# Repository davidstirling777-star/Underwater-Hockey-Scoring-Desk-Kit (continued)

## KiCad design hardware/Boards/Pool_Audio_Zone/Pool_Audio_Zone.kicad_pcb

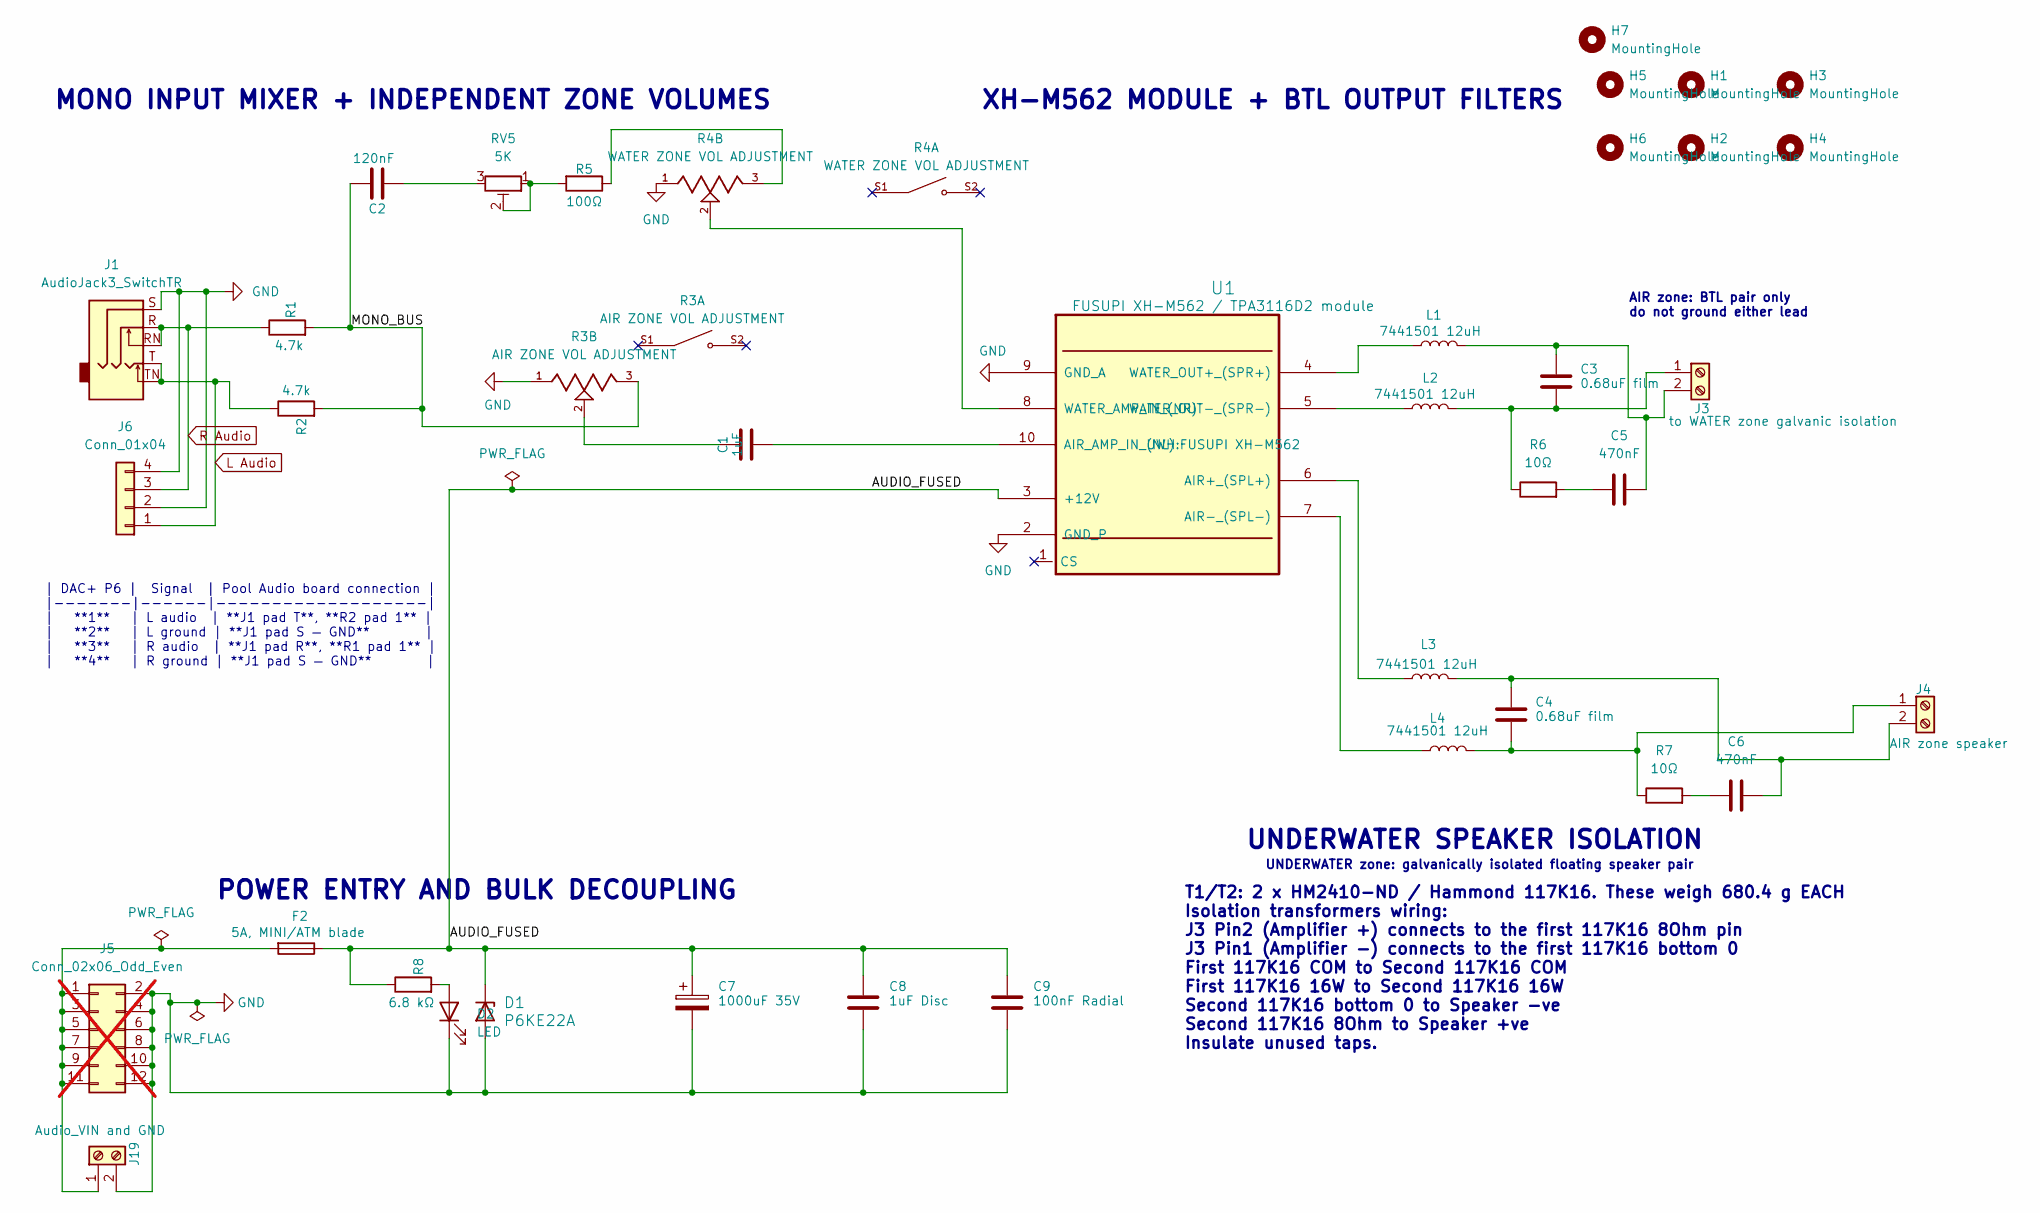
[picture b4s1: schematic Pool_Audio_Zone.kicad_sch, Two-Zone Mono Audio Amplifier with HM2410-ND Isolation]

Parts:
C1: 1uF; C_Rect_L7.2mm_W4.5mm_P5.00mm; MPN B32529C0105J000
C2: 120nF; C_Rect_L7.2mm_W3.5mm_P5.00mm; MPN R82EC3120DQ70J
C3, C4: 0.68uF film; C_Rect_L18.0mm_W9.0mm_P15.00mm_FKS3_FKP3; MPN B32652A3684K000
C5, C6: 470nF; C_Rect_L18.0mm_W9.0mm_P15.00mm_FKS3_FKP3; MPN B32672L4474J000
C7: 1000uF 35V; CP_Radial_D12.5mm_P5.00mm; MPN 35ZLH1000MEFC12.5X20
C8: 1uF Disc; C_Disc_D6.0mm_W4.4mm_P5.00mm; MPN RCER71H105K2K1H03B
C9: 100nF Radial; C_Disc_D4.7mm_W2.5mm_P5.00mm; MPN RDER71H104K0M1H03A
D1: P6KE22A; D_DO-15_P10.16mm_Horizontal; MPN P6KE22A
D2: LED; LED_D3.0mm; MPN WP710A10LCGDK
F2: 5A, MINI/ATM blade; Fuseholder_Blade_Mini_Keystone_3568; MPN 3568
H1, H2, H3, H4, H5, H6, H7: MountingHole; MountingHole_3.2mm_M3
J1: AudioJack3_SwitchTR; Jack_3.5mm_CUI_SJ1-3525N_Horizontal; MPN SJ1-3525N
J3: to WATER zone galvanic isolation; TerminalBlock_CUI_TB007-508-02_1x02_P5.08mm_Horizontal; MPN TB007-508-02BE
J4: AIR zone speaker; TerminalBlock_CUI_TB007-508-02_1x02_P5.08mm_Horizontal; MPN TB007-508-02BE
J5: Conn_02x06_Odd_Even; PinHeader_2x06_P2.54mm_Vertical; MPN TSW-106-07-F-D; not fitted
J6: Conn_01x04; PinHeader_1x04_P2.54mm_Vertical; MPN M20-9990445
J19: Audio_VIN and GND; TerminalBlock_CUI_TB007-508-02_1x02_P5.08mm_Horizontal; MPN TB007-508-02BE
L1, L2, L3, L4: 7441501 12uH; L_Toroid_Vertical_L28.6mm_W14.3mm_P11.43mm_Bourns_5700; MPN 7441501
R1, R2: 4.7k; R_Axial_DIN0207_L6.3mm_D2.5mm_P7.62mm_Horizontal; MPN MFR-25FBF52-4K7
R3: AIR ZONE VOL ADJUSTMENT; TRIM_PTN24B-C1015DPA; MPN PTN24B-C1015DA
R4: WATER ZONE VOL ADJUSTMENT; TRIM_PTN24B-C1015DPA; MPN PTN24B-C1015DA
R5: 100Ω; R_Axial_DIN0207_L6.3mm_D2.5mm_P10.16mm_Horizontal; MPN MFR-25FBF52-100R
R6, R7: 10Ω; TE_MPC5_Radial_P5.08mm_aligned; MPN MPC52100J
R8: 6.8 kΩ; R_Axial_DIN0207_L6.3mm_D2.5mm_P7.62mm_Horizontal; MPN MFR-25FRF52-6K8
RV5: 5K; Potentiometer_Bourns_3296W_Vertical; MPN 3296W-1-502LF
U1: FUSUPI XH-M562 / TPA3116D2 module; FUSUPI XH-M562

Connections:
/AUDIO_FUSED: C7.1, C8.1, C9.1, D1.1 (K), F2.1, R8.1, U1.3 (+12V)
/MONO_BUS: C2.1, R1.2, R2.2, R3.3
GND: C7.2, C8.2, C9.2, D1.2 (A), D2.1 (K), J1.S, J5.2, J5.4, J5.6, J5.8, J5.10, J5.12, J6.2, J6.4, J19.2, R3.1, R4.1, U1.2 (GND_P), U1.9 (GND_A)
L Audio: J1.T, J1.TN, J6.1, R2.1
unnamed: C1.1, R3.2
unnamed: C2.2, RV5.3
unnamed: C5.1, R6.2
unnamed: C6.1, R7.2
unnamed: D2.2 (A), R8.2
unnamed: C3.2, J3.1, L2.2, R6.1
unnamed: C3.1, C5.2, J3.2, L1.2
unnamed: C4.2, J4.1, L4.2, R7.1
unnamed: C4.1, C6.2, J4.2, L3.2
unnamed: F2.2, J5.1, J5.3, J5.5, J5.7, J5.9, J5.11, J19.1
unnamed: R4.3, R5.1
unnamed: R5.2, RV5.1, RV5.2
unnamed: L3.1, U1.6 (AIR+_(SPL+))
unnamed: L4.1, U1.7 (AIR-_(SPL-))
unnamed: C1.2, U1.10 (AIR_AMP_IN_(NL))
unnamed: R4.2, U1.8 (WATER_AMP_IN_(NR))
unnamed: L1.1, U1.4 (WATER_OUT+_(SPR+))
unnamed: L2.1, U1.5 (WATER_OUT-_(SPR-))
R Audio: J1.R, J1.RN, J6.3, R1.1

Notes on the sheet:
XH-M562 MODULE + BTL OUTPUT FILTERS
| DAC+ P6 | Signal | Pool Audio board connection | |-------|------|-------------------| | **1** | L audio | **J1 pad T**, **R2 pad 1** | | **2** | L ground | **J1 pad S — GND** | | **3** | R audio | **J1 pad R**, **R1 pad 1** | | **4** | R ground | **J1 pad S — GND** |
POWER ENTRY AND BULK DECOUPLING
UNDERWATER zone: galvanically isolated floating speaker pair
MONO INPUT MIXER + INDEPENDENT ZONE VOLUMES
UNDERWATER SPEAKER ISOLATION
AIR zone: BTL pair only do not ground either lead
T1/T2: 2 x HM2410-ND / Hammond 117K16. These weigh 680.4 g EACH Isolation transformers wiring: J3 Pin2 (Amplifier +) connects to the first 117K16 8Ohm pin J3 Pin1 (Amplifier -) connects to the first 117K16 bottom 0 First 117K16 COM to Second 117K16 COM First 117K16 16W to Second 117K16 16W Second 1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

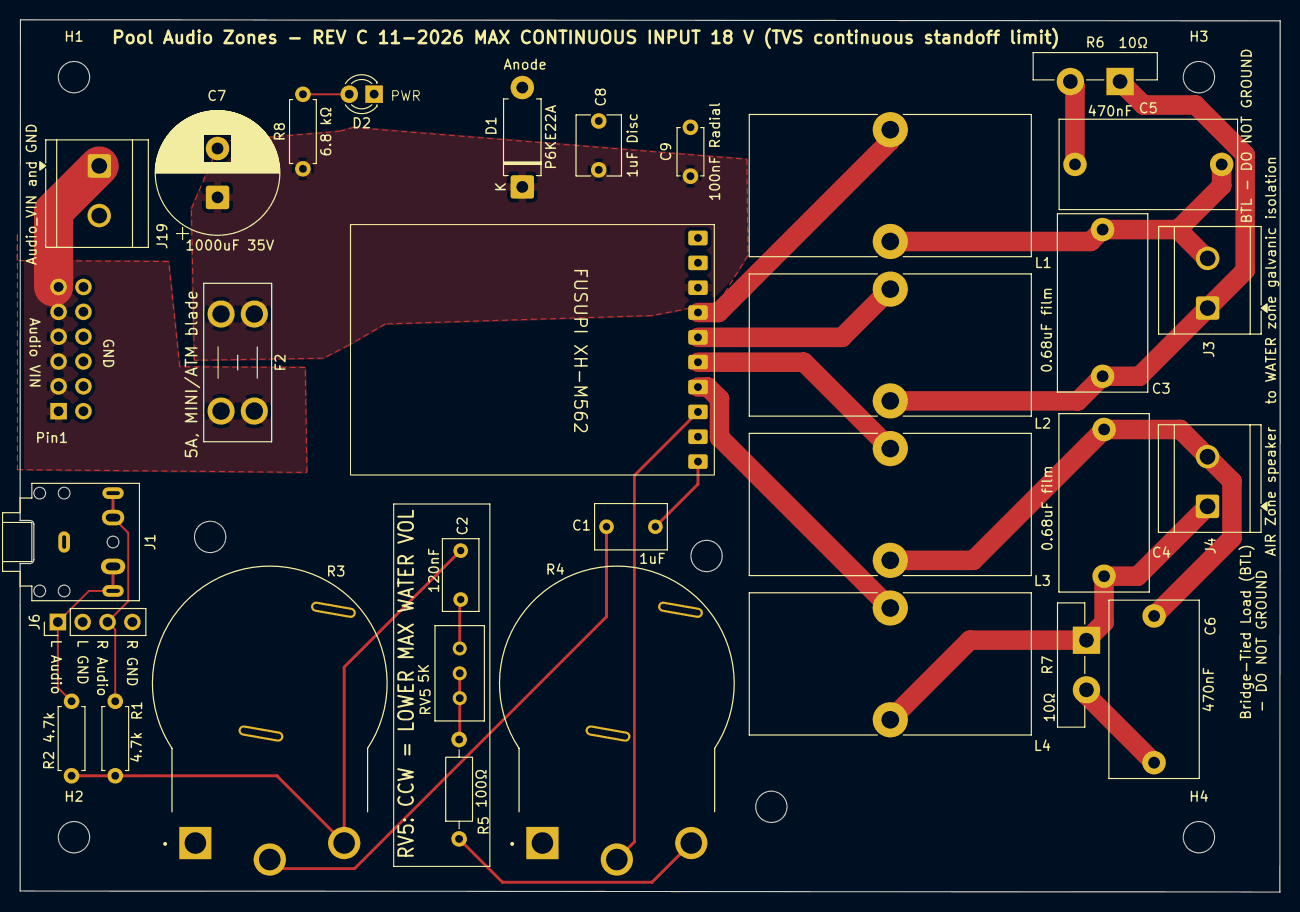
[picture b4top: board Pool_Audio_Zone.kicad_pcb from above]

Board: 2 copper layers, 128.8 x 89.2 mm, 39 parts (1 on the bottom side), 23 nets.

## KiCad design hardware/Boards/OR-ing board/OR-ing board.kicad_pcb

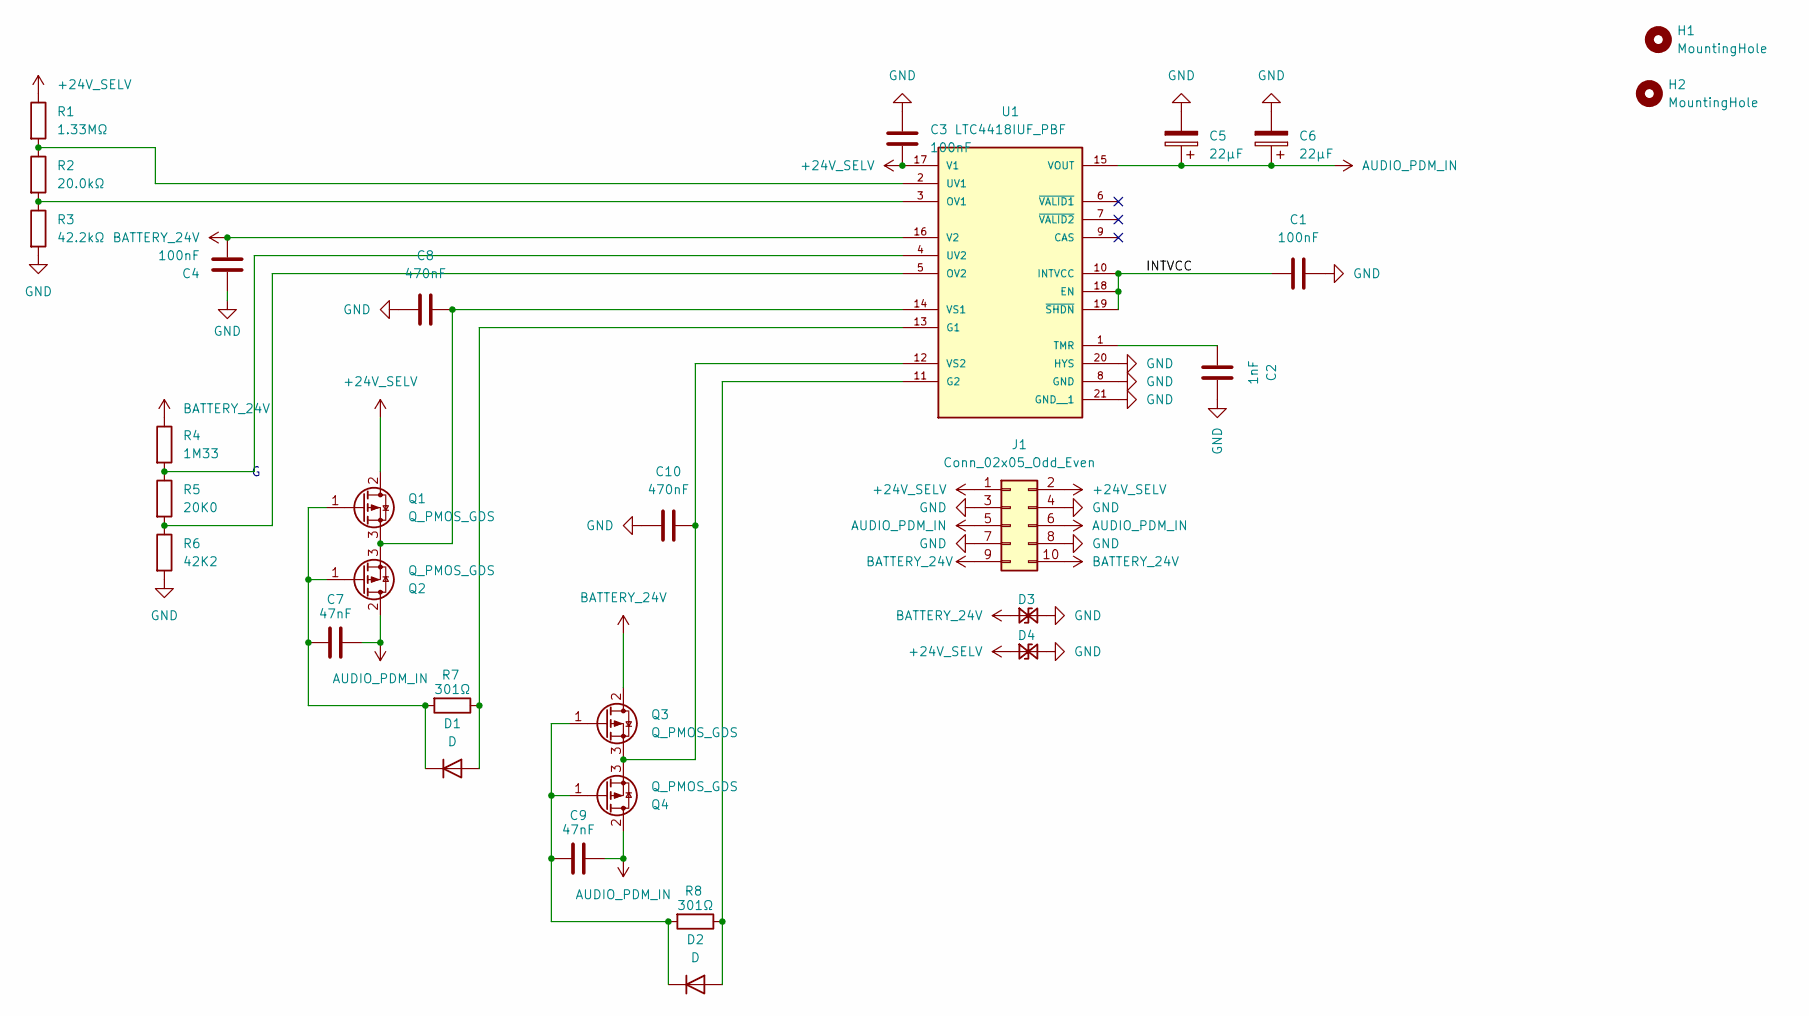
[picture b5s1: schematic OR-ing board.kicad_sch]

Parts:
C1, C3, C4: 100nF; C_0603_1608Metric; MPN CC0603KRX7R0BB104
C2: 1nF; C_0603_1608Metric; MPN 0603CG102J500NT
C5, C6: 22µF; CP_Elec_6.3x5.8; MPN EEHZC1H220P
C7, C9: 47nF; C_0603_1608Metric; MPN CC0603KRX7R9BB473
C8, C10: 470nF; C_0805_2012Metric; MPN 08051C474KAT2A
D1, D2: D; D_SOD-323F; MPN BAT46WJ,115
D3, D4: D; D_SMB; MPN SMBJ36CA
H1, H2: MountingHole; MountingHole_3.2mm_M3
J1: Conn_02x05_Odd_Even; PinHeader_2x05_P2.54mm_Vertical; MPN TSW-105-07-G-D
Q1, Q2, Q3, Q4: Q_PMOS_GDS; TO-252-2; MPN SQD50P06-15L_GE3
R1: 1.33MΩ; R_0603_1608Metric; MPN RC0603FR-071M33L
R2: 20.0kΩ; R_0603_1608Metric; MPN RC0603FR-0720KL
R3: 42.2kΩ; R_0603_1608Metric; MPN RC0603FR-0742K2L
R4: 1M33; R_0603_1608Metric; MPN RC0603FR-071M33L
R5: 20K0; R_0603_1608Metric; MPN RC0603FR-0720KL
R6: 42K2; R_0603_1608Metric; MPN RC0603FR-0742K2L
R7, R8: 301Ω; R_0603_1608Metric; MPN 0603WAF3010T5E
U1: LTC4418IUF_PBF; QFN50P400X400X80-21N; PARTREV A

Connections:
+24V_SELV: C3.2, D4.1 (A1), J1.1, J1.2, Q1.2 (D), R1.1, U1.17 (V1)
/INTVCC: C1.1, U1.10 (INTVCC), U1.18 (EN), U1.19 (~SHDN)
AUDIO_PDM_IN: C5.1, C6.1, C7.2, C9.2, J1.5, J1.6, Q2.2 (D), Q4.2 (D), U1.15 (VOUT)
BATTERY_24V: C4.2, D3.1 (A1), J1.9, J1.10, Q3.2 (D), R4.1, U1.16 (V2)
GND: C1.2, C2.2, C3.1, C4.1, C5.2, C6.2, C8.1, C10.1, D3.2 (A2), D4.2 (A2), J1.3, J1.4, J1.7, J1.8, R3.2, R6.2, U1.8 (GND), U1.20 (HYS), U1.21 (GND__1)
unnamed: D1.2 (A), R7.1, U1.13 (G1)
unnamed: C7.1, D1.1 (K), Q1.1 (G), Q2.1 (G), R7.2
unnamed: D2.2 (A), R8.1, U1.11 (G2)
unnamed: C9.1, D2.1 (K), Q3.1 (G), Q4.1 (G), R8.2
unnamed: C8.2, Q1.3 (S), Q2.3 (S), U1.14 (VS1)
unnamed: C10.2, Q3.3 (S), Q4.3 (S), U1.12 (VS2)
unnamed: R2.2, R3.1, U1.3 (OV1)
unnamed: R5.2, R6.1, U1.5 (OV2)
unnamed: C2.1, U1.1 (TMR)
unnamed: R1.2, R2.1, U1.2 (UV1)
unnamed: R4.2, R5.1, U1.4 (UV2)

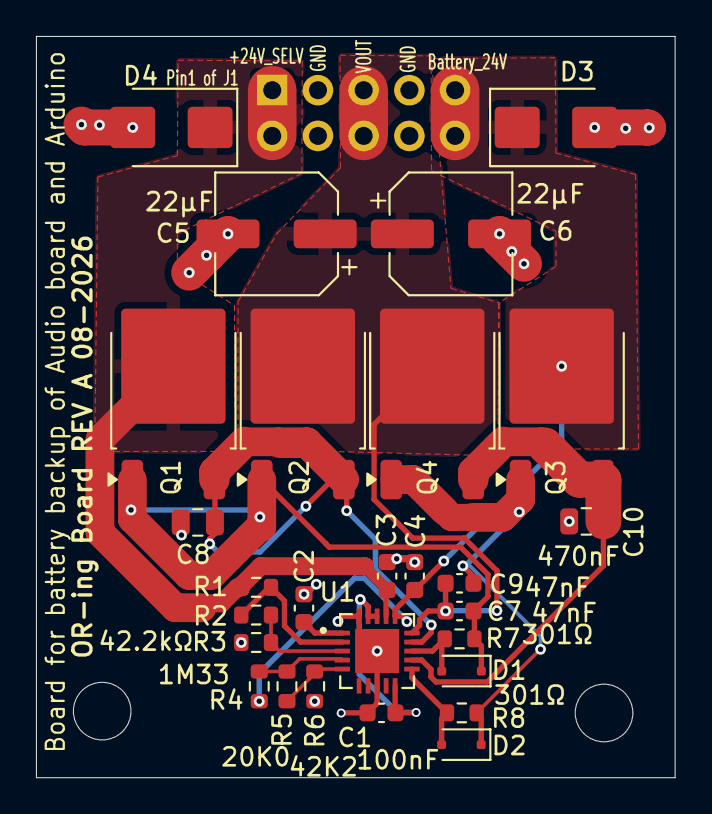
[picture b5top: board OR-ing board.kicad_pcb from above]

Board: 2 copper layers, 35.5 x 41.2 mm, 30 parts (1 on the bottom side), 16 nets.
